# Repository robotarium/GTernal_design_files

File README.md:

# GTernal

If looking to purchase circuit boards, this link may hold an up to date CircuitHub order: https://circuithub.com/projects/Payday02/GTernal/revisions/51452/parts

Link to slightly older version with more testing: https://circuithub.com/projects/Payday02/Gritsbot-3/revisions/50001/parts

If looking for a BOM, it can be found in the Parts Folder or here on google sheets (Google sheets may likely be more up to date than the parts folder as parts go in and out of circulation) https://docs.google.com/spreadsheets/d/1fcbRilmKaX-AO9ylUm2N9gINN3ZsyIf4CjUE0T1iR2c/edit?usp=sharing

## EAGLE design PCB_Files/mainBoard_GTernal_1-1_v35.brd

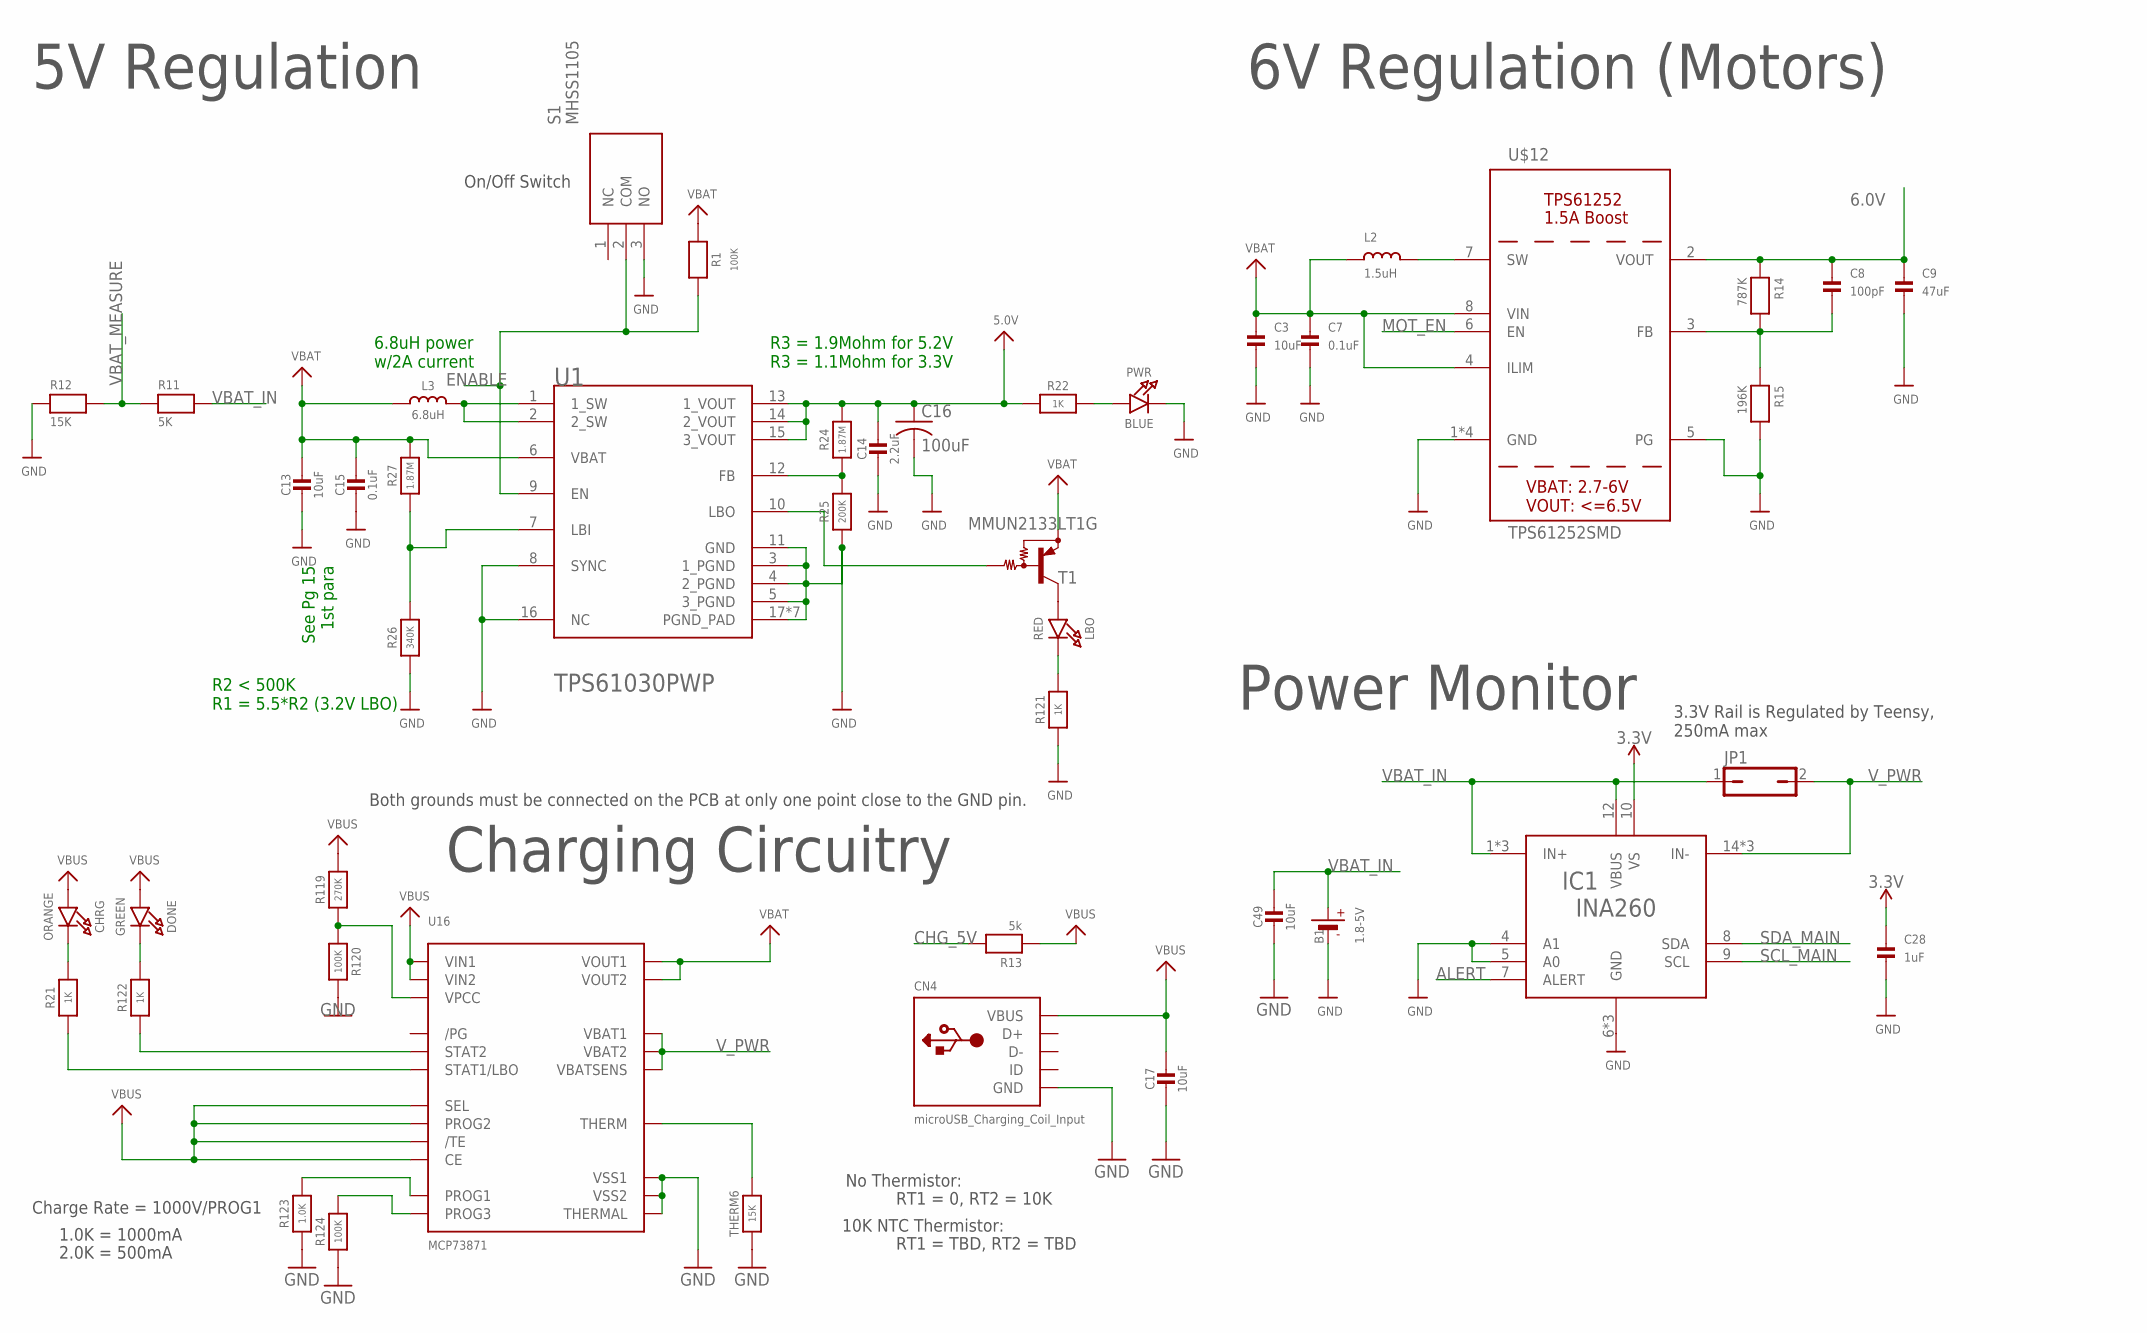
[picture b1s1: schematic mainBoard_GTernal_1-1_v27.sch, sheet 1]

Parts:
B1: 1.8-5V; JSTPH2
C3: 10uF; 0603
C7: 0.1uF; 0805
C8: 100pF; 0603
C9: 47uF; 1206
C13, C17, C49: 10uF; 0805-NO
C14: 2.2uF; 0805-NO
C15: 0.1uF; 0805_10MGAP
C16: 100uF; C1210
C28: 1uF; 0603-NO
CHRG: ORANGE; CHIPLED_0805_NOOUTLINE
CN4: microUSB_Charging_Coil_Input; 4UCONN_20329
DONE: GREEN; CHIPLED_0805_NOOUTLINE
IC1: INA260; TSSOP16
JP1: JP1Q; JP1
L2: 1.5uH; MURATA_DFE252012P-1R5M=P2
L3: 6.8uH; INDUCTOR_5X5MM_TDK_VLC5045
LBO: RED; CHIPLED_0805_NOOUTLINE
PWR: BLUE; CHIPLED_0805_NOOUTLINE
R1, R120, R124: 100K; 0805-NO
R11: 5K; 0805
R12: 15K; 0805
R13: 5k; 0805
R14: 787K; 0805
R15: 196K; 0805
R21, R22, R121, R122: 1K; 0805-NO
R24: 1.87M; 0805-NO
R25: 200K; 0805-NO
R26: 340K; _0805MP
R27: 1.87M; _0805MP
R119: 270K; 0805-NO
R123: 1.0K; 0805-NO
S1: MHSS1105
T1: MMUN2133LT1G; SC59-BEC
THERM6: 15K; 0805-NO
U1: TEXAS_INSTRUMENTS_TPS61030PWPTEXAS_INSTRUMENTS_TP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; TEXAS_INSTRUMENTS_TPS61030PWP_0
U16: MCP73871; QFN20_4MM
U$12: TPS61252SMD; TPS61252

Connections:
3.3V: C28.1, IC1.10 (VS); also elsewhere on the board
5.0V: C14.1, C16.1, R22.1, R24.2, U1.13 (1_VOUT), U1.14 (2_VOUT), U1.15 (3_VOUT); also elsewhere on the board
6.0V: C8.1, C9.1, R14.1, U$12.2 (VOUT); also elsewhere on the board
ALERT: IC1.7 (ALERT)
CHG_5V: R13.2; also elsewhere on the board
ENABLE: R1.2, S1.2 (COM), U1.9 (EN)
GND: B1.1 (-), C3.2, C7.2, C9.2, C13.2, C14.2, C15.2, C16.2, C17.2, C28.2, C49.2, CN4.BASE@1 (GND), CN4.BASE@2 (GND), CN4.GND, CN4.SPRT@1 (GND), CN4.SPRT@2 (GND), CN4.SPRT@3 (GND), CN4.SPRT@4 (GND), IC1.4 (A1), IC1.5 (A0), IC1.6 (GND), IC1.11 (GND), IC1.13 (GND), PWR.C, R12.1, R15.2, R25.1, R26.1, R120.2, R121.1, R123.1, R124.1, S1.3 (NO), THERM6.1, U1.3 (1_PGND), U1.4 (2_PGND), U1.5 (3_PGND), U1.8 (SYNC), U1.11 (GND), U1.16 (NC), U1.17 (PGND_PAD), U1.PAD_1 (PGND_PAD), U1.PAD_2 (PGND_PAD), U1.PAD_3 (PGND_PAD), U1.PAD_4 (PGND_PAD), U1.PAD_5 (PGND_PAD), U1.PAD_6 (PGND_PAD), U16.P$10 (VSS1), U16.P$11 (VSS2), U16.P$21 (THERMAL), U$12.1 (GND), U$12.5 (PG), U$12.P$2_GND (GND), U$12.P$3_GND (GND), U$12.THERMAL_GND (GND); also elsewhere on the board
MOT_EN: U$12.6 (EN); also elsewhere on the board
unnamed: R24.1, R25.2, U1.12 (FB)
unnamed: LBO.A, T1.C
unnamed: T1.B, U1.10 (LBO)
unnamed: CHRG.C, R21.2
unnamed: L2.P$2 (2), U$12.7 (SW)
unnamed: C8.2, R14.2, R15.1, U$12.3 (FB)
unnamed: L3.P$2 (2), U1.1 (1_SW), U1.2 (2_SW)
unnamed: R26.2, R27.1, U1.7 (LBI)
unnamed: PWR.A, R22.2
unnamed: R119.1, R120.1, U16.P$2 (VPCC)
unnamed: R122.1, U16.P$7 (STAT2)
unnamed: R21.1, U16.P$8 (STAT1/LBO)
unnamed: R123.2, U16.P$13 (PROG1)
unnamed: THERM6.2, U16.P$5 (THERM)
unnamed: DONE.C, R122.2
unnamed: LBO.C, R121.2
unnamed: R124.2, U16.P$12 (PROG3)
SCL_MAIN: IC1.9 (SCL); also elsewhere on the board
SDA_MAIN: IC1.8 (SDA); also elsewhere on the board
VBAT: C3.1, C7.1, C13.1, C15.1, L2.P$1 (1), L3.P$1 (1), R1.1, R27.2, T1.E, U1.6 (VBAT), U16.P$1 (VOUT1), U16.P$20 (VOUT2), U$12.4 (ILIM), U$12.8 (VIN); also elsewhere on the board
VBAT_IN: B1.2 (+), C49.1, IC1.1 (IN+), IC1.2 (IN+), IC1.3 (IN+), IC1.12 (VBUS), JP1.1, R11.2
VBAT_MEASURE: R11.1, R12.2; also elsewhere on the board
VBUS: C17.1, CHRG.A, CN4.VBUS, DONE.A, R13.1, R119.2, U16.P$3 (SEL), U16.P$4 (PROG2), U16.P$9 (/TE), U16.P$17 (CE), U16.P$18 (VIN1), U16.P$19 (VIN2)
V_PWR: IC1.14 (IN-), IC1.15 (IN-), IC1.16 (IN-), JP1.2, U16.P$14 (VBAT1), U16.P$15 (VBAT2), U16.P$16 (VBATSENS)

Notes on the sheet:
R2 < 500K R1 = 5.5*R2 (3.2V LBO)
Charging Circuitry
5V Regulation
6V Regulation (Motors)
Charge Rate = 1000V/PROG1
1.0K = 1000mA
2.0K = 500mA
No Thermistor:
10K NTC Thermistor:
RT1 = 0, RT2 = 10K
RT1 = TBD, RT2 = TBD
Both grounds must be connected on the PCB at only one point close to the GND pin.
On/Off Switch
See Pg 15 1st para
6.8uH power w/2A current
R3 = 1.9Mohm for 5.2V R3 = 1.1Mohm for 3.3V
Power Monitor
3.3V Rail is Regulated by Teensy, 250mA max

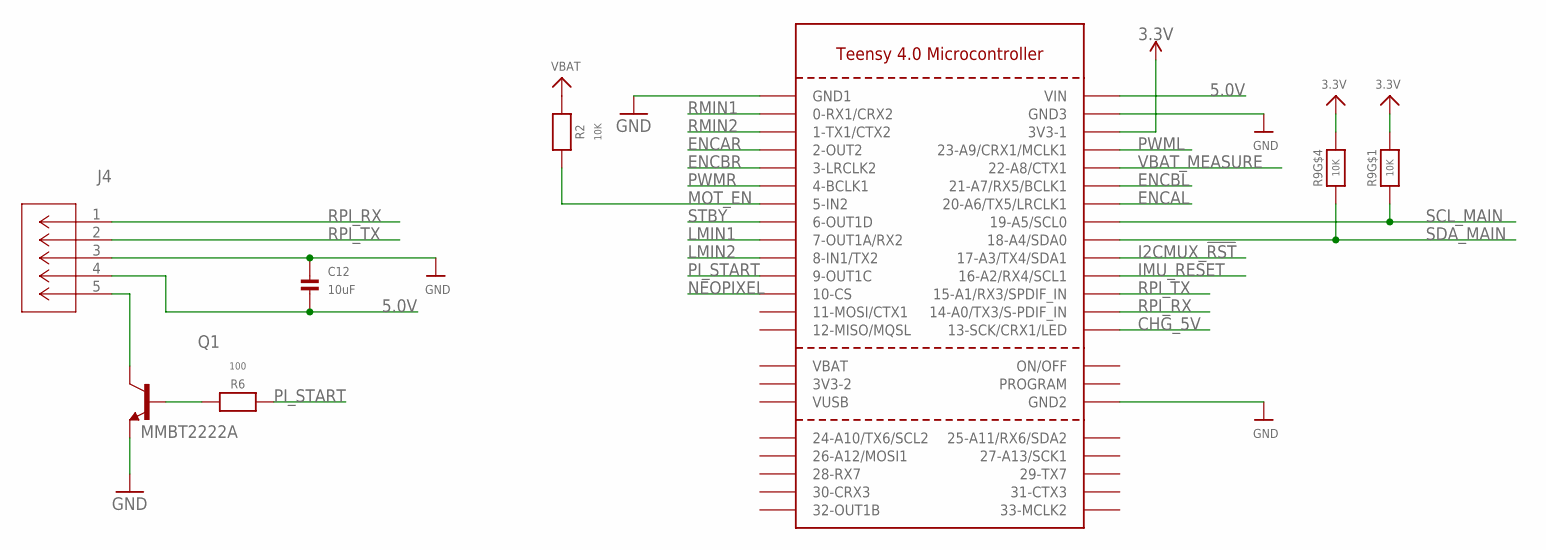
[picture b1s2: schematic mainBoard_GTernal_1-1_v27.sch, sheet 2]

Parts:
C12: 10uF; 0603
J4: 3A/250V; CONN_B5B-XH-A_JST
Q1: MMBT2222A; SOT23
R2: 10K; 0805-NO
R6: 100; 0805-NO
R9: 10K; RESPACK_4X0603
U$57: TEENSY40

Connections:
3.3V: R9.1, R9.4 (1), U$57.3V3-1; also elsewhere on the board
5.0V: C12.2, J4.4, U$57.VIN; also elsewhere on the board
CHG_5V: U$57.13-SCK/CRX1/LED; also elsewhere on the board
ENCAL: U$57.20-A6/TX5/LRCLK1; also elsewhere on the board
ENCAR: U$57.2-OUT2; also elsewhere on the board
ENCBL: U$57.21-A7/RX5/BCLK1; also elsewhere on the board
ENCBR: U$57.3-LRCLK2; also elsewhere on the board
GND: C12.1, J4.3, Q1.2 (E), U$57.GND1, U$57.GND2, U$57.GND3; also elsewhere on the board
I2CMUX_!RST: U$57.17-A3/TX4/SDA1; also elsewhere on the board
IMU_RESET: U$57.16-A2/RX4/SCL1; also elsewhere on the board
LMIN1: U$57.7-RX2/OUT1A (7-OUT1A/RX2); also elsewhere on the board
LMIN2: U$57.8-TX2/IN1 (8-IN1/TX2); also elsewhere on the board
MOT_EN: R2.2, U$57.5-IN2; also elsewhere on the board
unnamed: Q1.1 (B), R6.1
unnamed: J4.5, Q1.3 (C)
NEOPIXEL: U$57.10-CS/MQSR (10-CS); also elsewhere on the board
PI_START: R6.2, U$57.9-OUT1C
PWML: U$57.23-A9/CRX1/CCLK1 (23-A9/CRX1/MCLK1); also elsewhere on the board
PWMR: U$57.4-BCLK2 (4-BCLK1); also elsewhere on the board
RMIN1: U$57.0-RX1 (0-RX1/CRX2); also elsewhere on the board
RMIN2: U$57.1-TX1 (1-TX1/CTX2); also elsewhere on the board
RPI_RX: J4.1, U$57.14-A0/TX3/S-PFI_OUT (14-A0/TX3/S-PDIF_IN)
RPI_TX: J4.2, U$57.15-A1/RX3/S-PDIF_IN (15-A1/RX3/SPDIF_IN)
SCL_MAIN: R9.8 (2), U$57.19-A5/SCL0; also elsewhere on the board
SDA_MAIN: R9.5 (2), U$57.18-A4/SDA0; also elsewhere on the board
STBY: U$57.6-OUT1D; also elsewhere on the board
VBAT: R2.1; also elsewhere on the board
VBAT_MEASURE: U$57.22-A8/CTX1; also elsewhere on the board

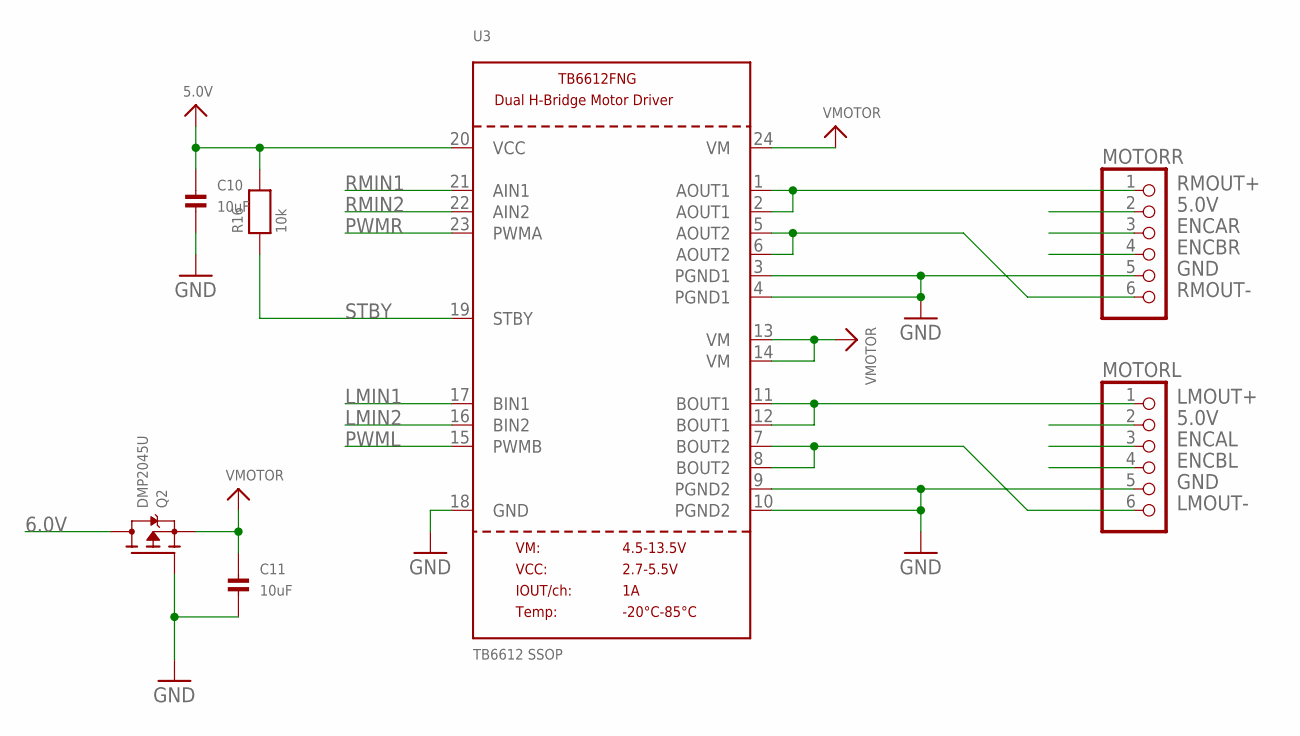
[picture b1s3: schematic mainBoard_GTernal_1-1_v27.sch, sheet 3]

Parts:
C10, C11: 10uF; 0603
MOTORL: PINHD-1X6CB; 1X06-CLEANBIG
MOTORR: PINHD-1X6CB; 1X06-CLEANBIG
Q2: DMP2045U; SOT23-WIDE
R16: 10k; 0805
U3: TB6612 SSOP; SSOP24

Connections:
5.0V: C10.1, MOTORL.2, MOTORR.2, R16.2, U3.20 (VCC); also elsewhere on the board
6.0V: Q2.3 (D); also elsewhere on the board
ENCAL: MOTORL.3; also elsewhere on the board
ENCAR: MOTORR.3; also elsewhere on the board
ENCBL: MOTORL.4; also elsewhere on the board
ENCBR: MOTORR.4; also elsewhere on the board
GND: C10.2, C11.2, MOTORL.5, MOTORR.5, Q2.1 (G), U3.3 (PGND1), U3.4 (PGND1), U3.9 (PGND2), U3.10 (PGND2), U3.18 (GND); also elsewhere on the board
LMIN1: U3.17 (BIN1); also elsewhere on the board
LMIN2: U3.16 (BIN2); also elsewhere on the board
LMOUT+: MOTORL.1, U3.11 (BOUT1), U3.12 (BOUT1)
LMOUT-: MOTORL.6, U3.7 (BOUT2), U3.8 (BOUT2)
PWML: U3.15 (PWMB); also elsewhere on the board
PWMR: U3.23 (PWMA); also elsewhere on the board
RMIN1: U3.21 (AIN1); also elsewhere on the board
RMIN2: U3.22 (AIN2); also elsewhere on the board
RMOUT+: MOTORR.1, U3.1 (AOUT1), U3.2 (AOUT1)
RMOUT-: MOTORR.6, U3.5 (AOUT2), U3.6 (AOUT2)
STBY: R16.1, U3.19 (STBY); also elsewhere on the board
VMOTOR: C11.1, Q2.2 (S), U3.13 (VM), U3.14 (VM), U3.24 (VM)

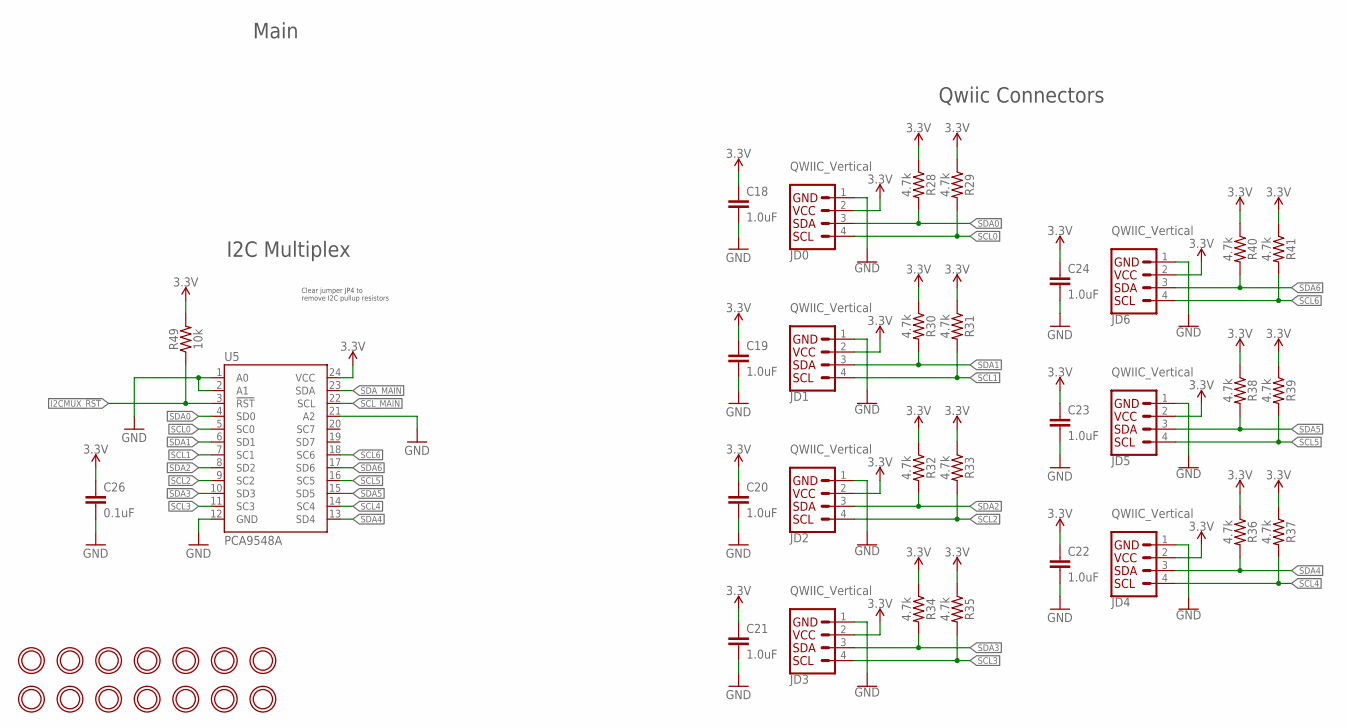
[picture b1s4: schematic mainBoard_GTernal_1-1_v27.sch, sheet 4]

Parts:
C18, C19, C20, C21, C22, C23, C24: 1.0uF; 0603
C26: 0.1uF; 0603
JD0, JD1, JD2, JD3, JD4, JD5, JD6: QWIIC_Vertical; JST04_1MM_VERT
R28, R29, R30, R31, R32, R33, R34, R35, R36, R37, R38, R39, R40, R41: 4.7k; 0603
R49: 10k; 0603
U5: PCA9548A; TSSOP28
U$8, U$30, U$31, U$32, U$33, U$34, U$35, U$36, U$37, U$43, U$45, U$46, U$47, U$48: MOUNTINGHOLE2.5; MOUNTINGHOLE_2.5_PLATED

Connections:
3.3V: C18.1, C19.1, C20.1, C21.1, C22.1, C23.1, C24.1, C26.1, JD0.2, JD1.2, JD2.2, JD3.2, JD4.2, JD5.2, JD6.2, R28.1, R29.1, R30.1, R31.1, R32.1, R33.1, R34.1, R35.1, R36.1, R37.1, R38.1, R39.1, R40.1, R41.1, R49.2, U5.24 (VCC); also elsewhere on the board
GND: C18.2, C19.2, C20.2, C21.2, C22.2, C23.2, C24.2, C26.2, JD0.1, JD1.1, JD2.1, JD3.1, JD4.1, JD5.1, JD6.1, U5.1 (A0), U5.2 (A1), U5.12 (GND), U5.21 (A2); also elsewhere on the board
I2CMUX_!RST: R49.1, U5.3 (!RST); also elsewhere on the board
SCL0: JD0.4, R29.2, U5.5 (SC0)
SCL1: JD1.4, R31.2, U5.7 (SC1)
SCL2: JD2.4, R33.2, U5.9 (SC2)
SCL3: JD3.4, R35.2, U5.11 (SC3)
SCL4: JD4.4, R37.2, U5.14 (SC4)
SCL5: JD5.4, R39.2, U5.16 (SC5)
SCL6: JD6.4, R41.2, U5.18 (SC6)
SCL_MAIN: U5.22 (SCL); also elsewhere on the board
SDA0: JD0.3, R28.2, U5.4 (SD0)
SDA1: JD1.3, R30.2, U5.6 (SD1)
SDA2: JD2.3, R32.2, U5.8 (SD2)
SDA3: JD3.3, R34.2, U5.10 (SD3)
SDA4: JD4.3, R36.2, U5.13 (SD4)
SDA5: JD5.3, R38.2, U5.15 (SD5)
SDA6: JD6.3, R40.2, U5.17 (SD6)
SDA_MAIN: U5.23 (SDA); also elsewhere on the board

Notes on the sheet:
Qwiic Connectors
Main
I2C Multiplex
Clear jumper JP4 to remove I2C pullup resistors

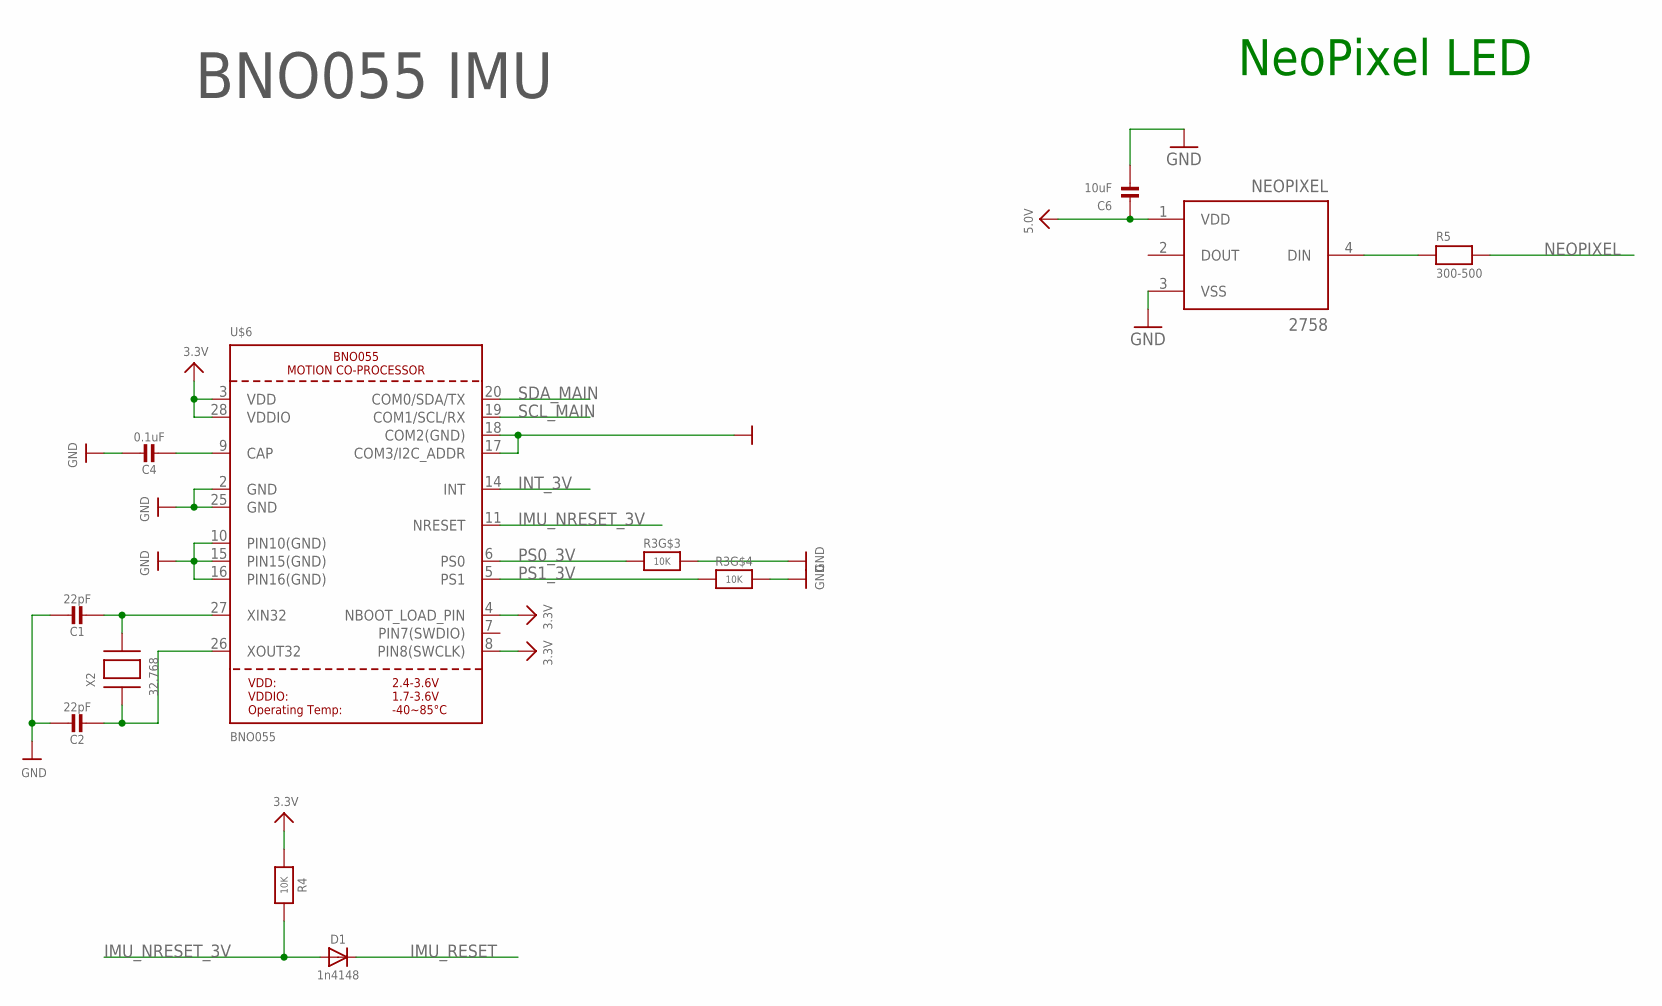
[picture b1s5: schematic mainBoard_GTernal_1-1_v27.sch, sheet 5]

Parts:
C1, C2: 22pF; 0603-NO
C4: 0.1uF; 0603-NO
C6: 10uF; 0603
D1: 1n4148; SOD-323
NEOPIXEL: 2758; SOL320P540X170-4N
R3: 10K; RESPACK_4X0603
R4: 10K; 0603-NO
R5: 300-500; 0805
U$6: BNO055
X2: 32.768; XTAL3215

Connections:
3.3V: R4.1, U$6.3 (VDD), U$6.4 (NBOOT_LOAD_PIN), U$6.8 (PIN8(SWCLK)), U$6.28 (VDDIO); also elsewhere on the board
5.0V: C6.1, NEOPIXEL.1 (VDD); also elsewhere on the board
GND: C1.1, C2.1, C4.1, C6.2, NEOPIXEL.3 (VSS), R3.5 (2), R3.6 (2), U$6.2 (GND), U$6.10 (PIN10(GND)), U$6.15 (PIN15(GND)), U$6.16 (PIN16(GND)), U$6.17 (COM3/I2C_ADDR), U$6.18 (COM2(GND)), U$6.25 (GND); also elsewhere on the board
IMU_NRESET_3V: D1.A, R4.2, U$6.11 (NRESET)
IMU_RESET: D1.C; also elsewhere on the board
INT_3V: U$6.14 (INT)
unnamed: C1.2, U$6.27 (XIN32), X2.P$2
unnamed: C2.2, U$6.26 (XOUT32), X2.P$1
unnamed: C4.2, U$6.9 (CAP)
unnamed: NEOPIXEL.4 (DIN), R5.1
NEOPIXEL: R5.2; also elsewhere on the board
PS0_3V: R3.3 (1), U$6.6 (PS0)
PS1_3V: R3.4 (1), U$6.5 (PS1)
SCL_MAIN: U$6.19 (COM1/SCL/RX); also elsewhere on the board
SDA_MAIN: U$6.20 (COM0/SDA/TX); also elsewhere on the board

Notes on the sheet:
BNO055 IMU
NeoPixel LED

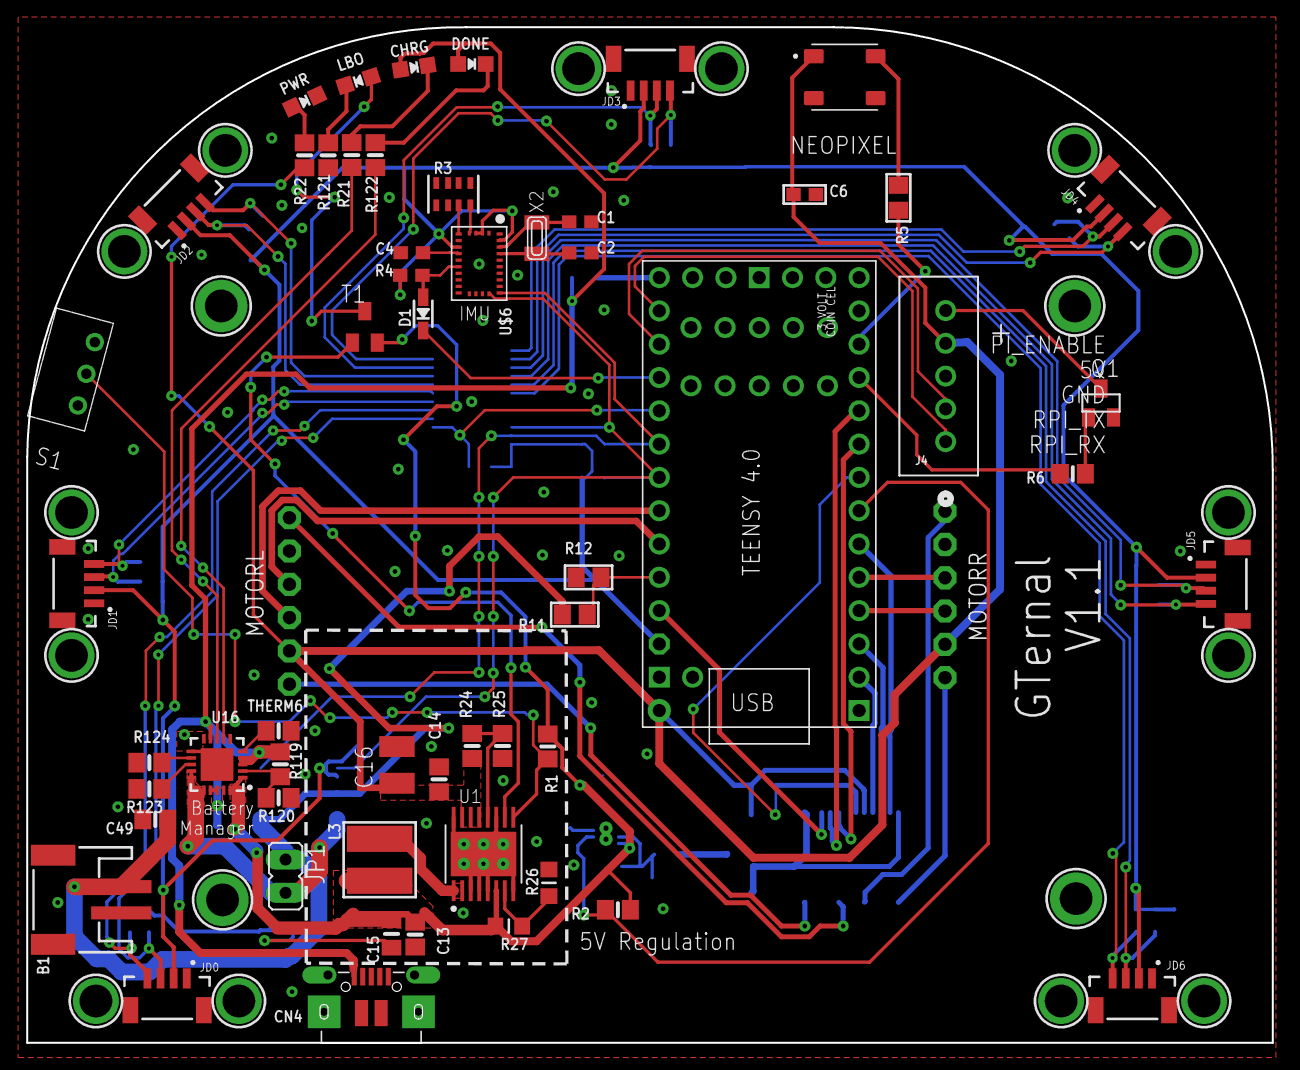
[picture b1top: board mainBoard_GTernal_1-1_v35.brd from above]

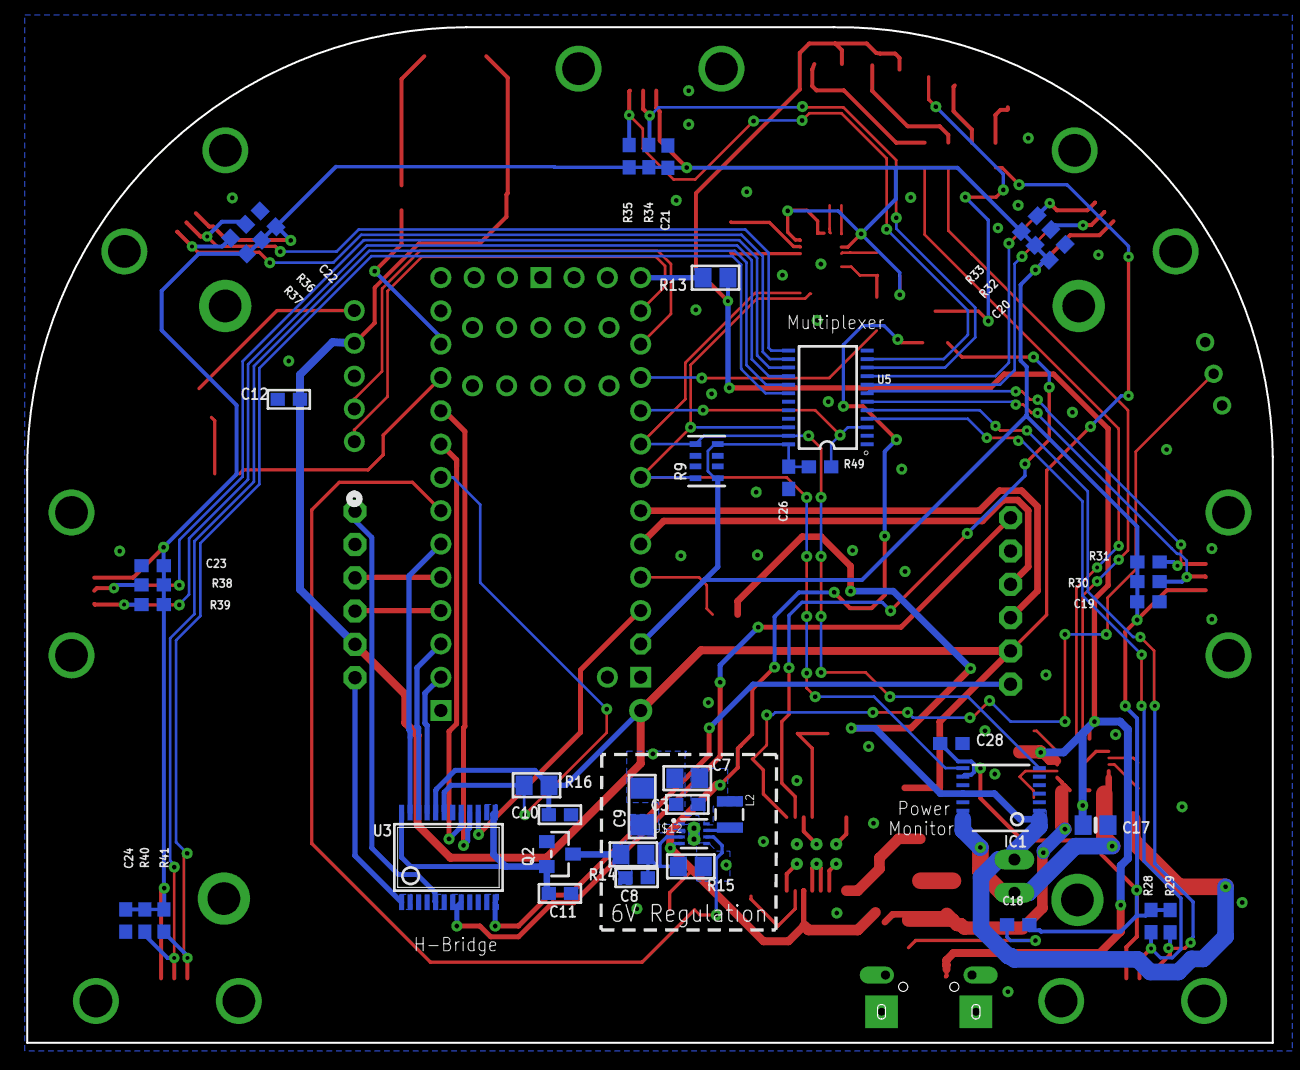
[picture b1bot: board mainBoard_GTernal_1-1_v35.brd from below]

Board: 2 copper layers, 95.0 x 77.5 mm, 119 parts (43 on the bottom side), 76 nets.

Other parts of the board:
U$7, U$23, U$28, U$29: MOUNTINGHOLE_2.5_PLATED_THICK

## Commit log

2023-09-28 Moved from GTernal repository
2023-10-17 Updated files with the most recent iteration
2024-04-28 Updated design files, documents, and BOM
2024-04-29 Updated the laser cutting files for the top plates
2024-10-07 Updated the assembly section
2024-10-07 Added new files for lasercutting and motor PID tuning via MATLAB
2025-09-26 Updated the lasercutting files

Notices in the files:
parts and their libraries:
SparkFun-Aesthetics: Licensing: Creative Commons ShareAlike 4.0 International - https://creativecommons.org/licenses/by-sa/4.0
microbuilder: This work is placed in the public domain, and may be freely used for commercial and non-commercial work with the following conditions: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
